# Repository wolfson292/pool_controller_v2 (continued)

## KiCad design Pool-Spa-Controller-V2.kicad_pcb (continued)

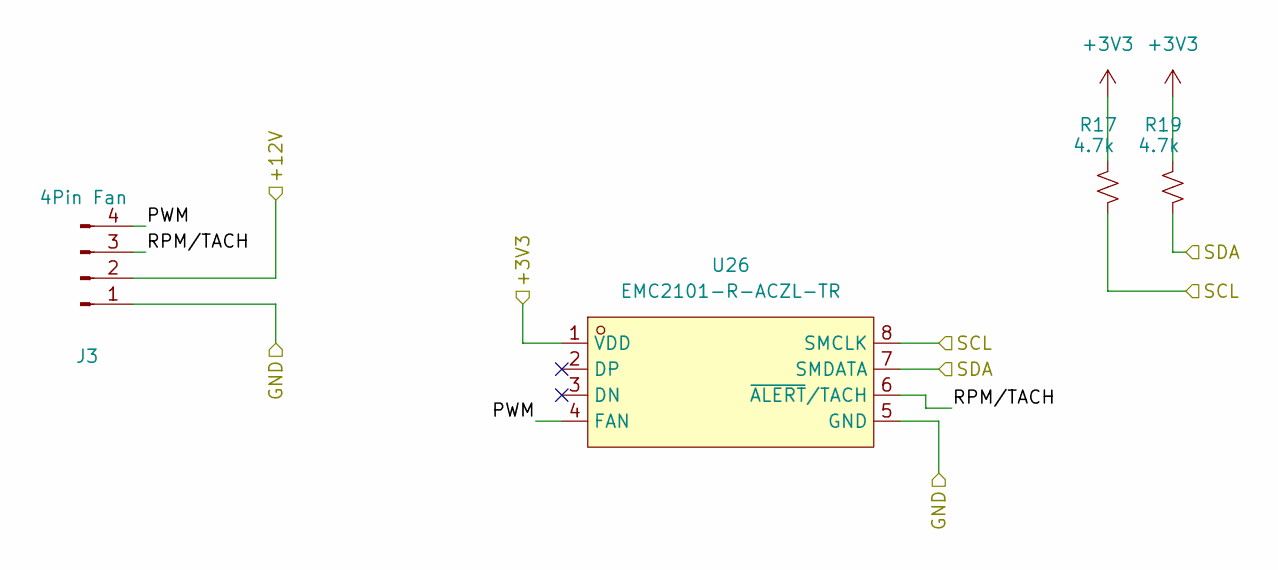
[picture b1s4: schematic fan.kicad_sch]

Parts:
J3: 4Pin Fan; PinHeader_1x04_P2.54mm_Vertical
R17, R19: 4.7k; R_0402_1005Metric
U26: EMC2101-R-ACZL-TR; MSOP-8_L3.0-W3.0-P0.65-LS4.9-BL; LCSC Part C626968

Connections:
+3V3: R17.1, R19.1, U26.1 (VDD); also elsewhere on the board
+12V: J3.2; also elsewhere on the board
/Fan B/PWM: J3.4, U26.4 (FAN)
/Fan B/RPM/TACH: J3.3, U26.6 (~ALERT/TACH)
/SCL_1: R17.2, U26.8 (SMCLK); also elsewhere on the board
/SDA_1: R19.2, U26.7 (SMDATA); also elsewhere on the board
AGND: J3.1, U26.5 (GND); also elsewhere on the board

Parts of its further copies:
J2: 4Pin Fan; PinHeader_1x04_P2.54mm_Vertical
R18, R36: 4.7k; R_0402_1005Metric
U25: EMC2101-R-ACZL-TR; MSOP-8_L3.0-W3.0-P0.65-LS4.9-BL; LCSC Part C626968

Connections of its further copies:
+3V3: R18.1, R36.1, U25.1 (VDD); also elsewhere on the board
+12V: J2.2; also elsewhere on the board
/Fan A/PWM: J2.4, U25.4 (FAN)
/Fan A/RPM/TACH: J2.3, U25.6 (~ALERT/TACH)
/SCL_0: R18.2, U25.8 (SMCLK); also elsewhere on the board
/SDA_0: R36.2, U25.7 (SMDATA); also elsewhere on the board
AGND: J2.1, U25.5 (GND); also elsewhere on the board

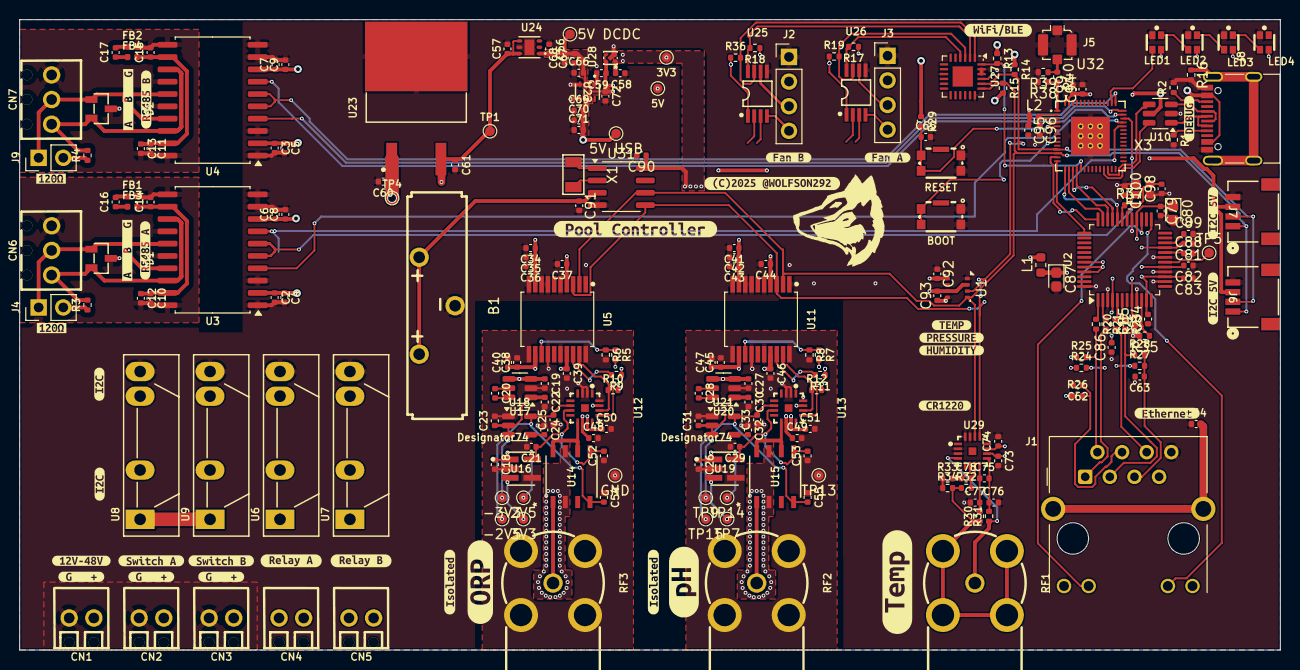
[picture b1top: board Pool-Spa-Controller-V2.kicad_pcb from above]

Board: 4 copper layers, 130.0 x 65.0 mm, 256 parts (0 on the bottom side), 123 nets.

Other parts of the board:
kibuzzard-67A4FAF6: G***; kibuzzard-67A4FAF6
kibuzzard-67A62A6B: G***; kibuzzard-67A62A6B
kibuzzard-67A6282B: G***; kibuzzard-67A6282B
kibuzzard-67A6283A: G***; kibuzzard-67A6283A
kibuzzard-67A62823: G***; kibuzzard-67A62823
kibuzzard-67A62993: G***; kibuzzard-67A62993
kibuzzard-67AA2F78, kibuzzard-67AA2F78#2: G***; kibuzzard-67AA2F78
kibuzzard-679A47BC, kibuzzard-679A47BC#2: G***; kibuzzard-679A47BC
kibuzzard-67990E4A: G***; kibuzzard-67990E4A
kibuzzard-67990EC5: G***; kibuzzard-67990EC5
kibuzzard-67990EE4, kibuzzard-67990EE4#2: G***; kibuzzard-67990EE4
kibuzzard-67990FDB, kibuzzard-67990FDB#2, kibuzzard-67990FDB#3: G***; kibuzzard-67990FDB
kibuzzard-679907BF: G***; kibuzzard-679907BF
kibuzzard-679913F9: G***; kibuzzard-679913F9
kibuzzard-6799077F, kibuzzard-6799077F#2: G***; kibuzzard-6799077F
kibuzzard-6799095B: G***; kibuzzard-6799095B
kibuzzard-6799099B, kibuzzard-6799099B#2: G***; kibuzzard-6799099B
kibuzzard-6799101C: G***; kibuzzard-6799101C
kibuzzard-6799102D: G***; kibuzzard-6799102D
kibuzzard-6799136C: G***; kibuzzard-6799136C
kibuzzard-67990939: G***; kibuzzard-67990939
kibuzzard-67990953: G***; kibuzzard-67990953
kibuzzard-67991013: G***; kibuzzard-67991013
kibuzzard-67991024: G***; kibuzzard-67991024
kibuzzard-67991399: G***; kibuzzard-67991399
kibuzzard-67991402: G***; kibuzzard-67991402
kibuzzard-67991438: G***; kibuzzard-67991438

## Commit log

2025-02-10 Add CERN-OHL-S License
2025-02-10 Remove old sch file
